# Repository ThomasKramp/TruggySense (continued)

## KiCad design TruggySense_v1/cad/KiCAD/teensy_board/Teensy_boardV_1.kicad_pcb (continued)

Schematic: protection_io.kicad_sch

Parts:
D18, D19, D34, D35, D36, D37, D38, D39: TVS_SMF3.3; SOD3718X108N
D40, D41, D42, D43, D44, D45, D46, D47: Zener_ZM4729A-GS18; D_MELF
F16, F17, F18, F19, F20, F21, F22, F23: SMD0805B010TF; Fuse_0805_2012Metric_Pad1.15x1.40mm_HandSolder

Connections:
/Encoder/Protection_IO/IN_1: D18.1 (K), F16.1; also elsewhere on the board
/Encoder/Protection_IO/IN_2: D19.1 (K), F17.1; also elsewhere on the board
/Encoder/Protection_IO/IN_3: D34.1 (K), F18.1; also elsewhere on the board
/Encoder/Protection_IO/IN_4: D35.1 (K), F19.1; also elsewhere on the board
/Encoder/Protection_IO/IN_5: D36.1 (K), F20.1; also elsewhere on the board
/Encoder/Protection_IO/IN_6: D37.1 (K), F21.1; also elsewhere on the board
/Encoder/Protection_IO/IN_7: D38.1 (K), F22.1; also elsewhere on the board
/Encoder/Protection_IO/IN_8: D39.1 (K), F23.1; also elsewhere on the board
/Encoder/Protection_IO/OUT_1: D40.1 (K), F16.2; also elsewhere on the board
/Encoder/Protection_IO/OUT_2: D41.1 (K), F17.2; also elsewhere on the board
/Encoder/Protection_IO/OUT_3: D42.1 (K), F18.2; also elsewhere on the board
/Encoder/Protection_IO/OUT_4: D43.1 (K), F19.2; also elsewhere on the board
/Encoder/Protection_IO/OUT_5: D44.1 (K), F20.2; also elsewhere on the board
/Encoder/Protection_IO/OUT_6: D45.1 (K), F21.2; also elsewhere on the board
/Encoder/Protection_IO/OUT_7: D46.1 (K), F22.2; also elsewhere on the board
/Encoder/Protection_IO/OUT_8: D47.1 (K), F23.2; also elsewhere on the board
GND: D18.2 (A), D19.2 (A), D34.2 (A), D35.2 (A), D36.2 (A), D37.2 (A), D38.2 (A), D39.2 (A), D40.2 (A), D41.2 (A), D42.2 (A), D43.2 (A), D44.2 (A), D45.2 (A), D46.2 (A), D47.2 (A); also elsewhere on the board

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
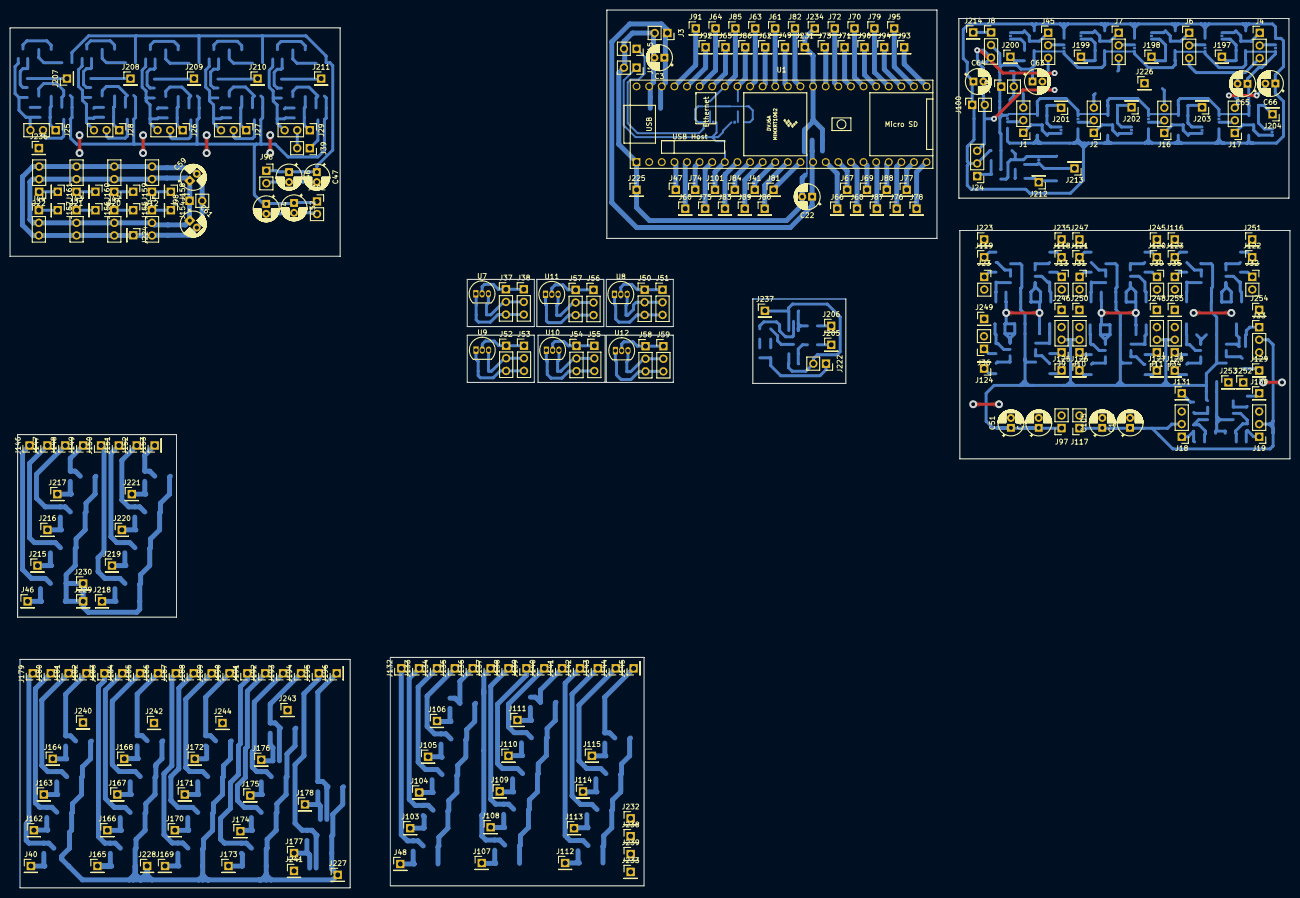
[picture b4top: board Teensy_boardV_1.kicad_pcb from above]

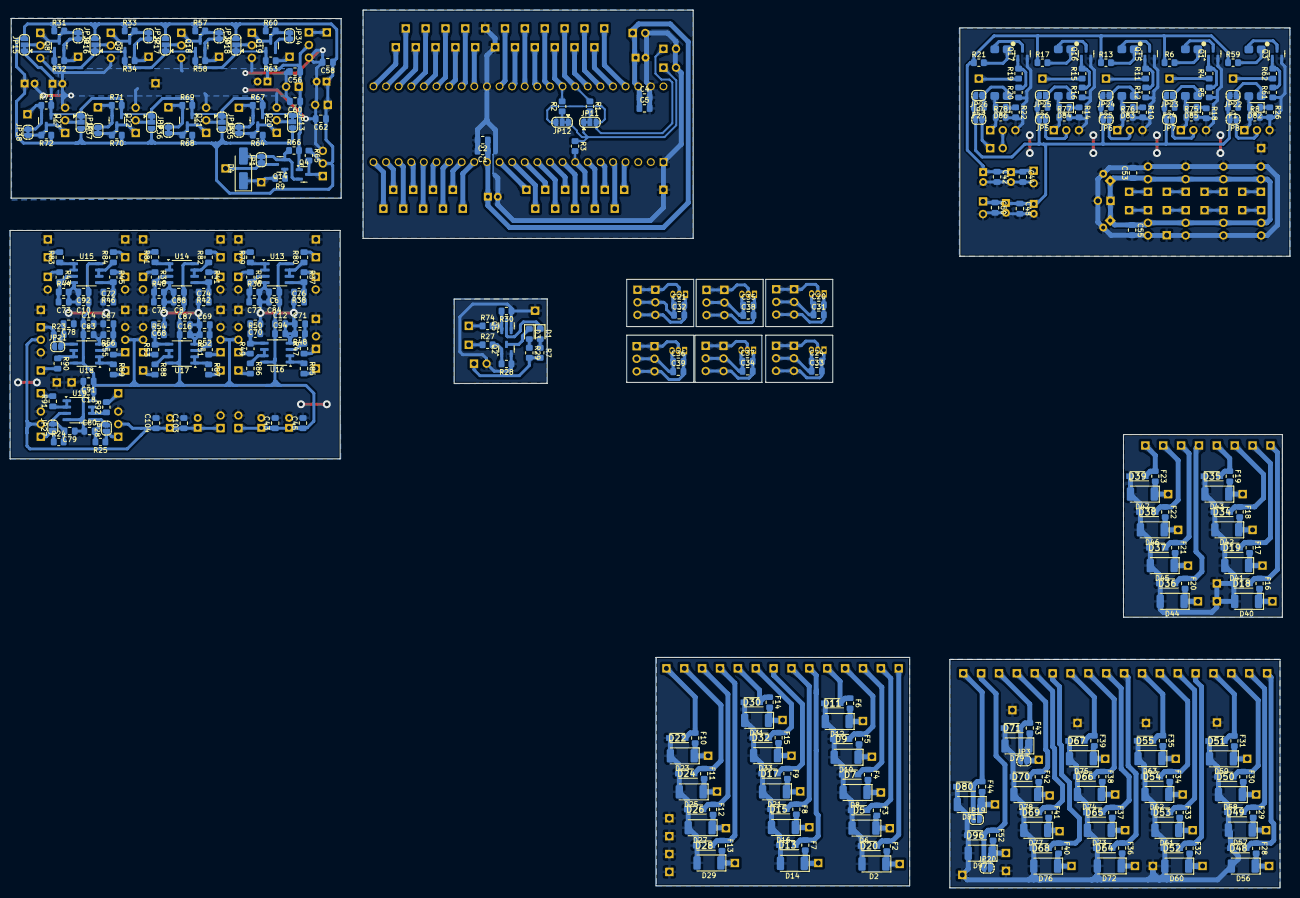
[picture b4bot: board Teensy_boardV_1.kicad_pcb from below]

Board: 2 copper layers, 257.8 x 176.8 mm, 625 parts (347 on the bottom side), 269 nets.

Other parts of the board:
C20, C21, C24, C34, C35, C36: 10µ; C_0805_2012Metric_Pad1.18x1.45mm_HandSolder
C31, C32, C33, C37, C38, C39: 10n; C_0805_2012Metric_Pad1.18x1.45mm_HandSolder
D48, D49, D50, D51, D52, D53, D54, D55, D64, D65, D66, D67, D68, D69, D70, D71, D80, D96: TVS_SMF3.3; SOD3718X108N
D56, D57, D58, D59, D60, D61, D62, D63, D72, D73, D74, D75, D76, D77, D78, D79, D81, D97: Zener_ZM4729A-GS18; D_MELF
F28, F29, F30, F31, F32, F33, F34, F35, F36, F37, F38, F39, F40, F41, F42, F43, F44, F52: SMD0805B010TF; Fuse_0805_2012Metric_Pad1.15x1.40mm_HandSolder
J37, J50, J52, J54, J56, J58: Temperature_module_in; PinHeader_1x03_P2.54mm_Vertical
J38, J51, J53, J55, J57, J59: Temperature_module_out; PinHeader_1x03_P2.54mm_Vertical
JP3, JP19, JP20: SolderJumper_2_Open; SolderJumper-2_P1.3mm_Open_RoundedPad1.0x1.5mm
U7, U8, U9, U10, U11, U12: DS18B20; TO-92_Inline

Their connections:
1_Wire_U: J37.1, J38.1, J50.1, J51.1, J52.1, J53.1, J54.1, J55.1, J56.1, J57.1, J58.1, J59.1, U7.2 (DQ), U8.2 (DQ), U9.2 (DQ), U10.2 (DQ), U11.2 (DQ), U12.2 (DQ); also elsewhere on the board
/Communication & pheripherals/Protection_IO1/IN_1: D48.1 (K), F28.1; also elsewhere on the board
/Communication & pheripherals/Protection_IO1/IN_2: D49.1 (K), F29.1; also elsewhere on the board
/Communication & pheripherals/Protection_IO1/IN_3: D50.1 (K), F30.1; also elsewhere on the board
/Communication & pheripherals/Protection_IO1/IN_4: D51.1 (K), F31.1; also elsewhere on the board
/Communication & pheripherals/Protection_IO1/IN_5: D52.1 (K), F32.1; also elsewhere on the board
/Communication & pheripherals/Protection_IO1/IN_6: D53.1 (K), F33.1; also elsewhere on the board
/Communication & pheripherals/Protection_IO1/IN_7: D54.1 (K), F34.1; also elsewhere on the board
/Communication & pheripherals/Protection_IO1/IN_8: D55.1 (K), F35.1; also elsewhere on the board
/Communication & pheripherals/Protection_IO1/IN_9: D64.1 (K), F36.1; also elsewhere on the board
/Communication & pheripherals/Protection_IO1/IN_10: D65.1 (K), F37.1; also elsewhere on the board
/Communication & pheripherals/Protection_IO1/IN_11: D66.1 (K), F38.1; also elsewhere on the board
/Communication & pheripherals/Protection_IO1/IN_12: D67.1 (K), F39.1; also elsewhere on the board
/Communication & pheripherals/Protection_IO1/IN_13: D68.1 (K), F40.1; also elsewhere on the board
/Communication & pheripherals/Protection_IO1/IN_14: D69.1 (K), F41.1; also elsewhere on the board
/Communication & pheripherals/Protection_IO1/IN_15: D70.1 (K), F42.1; also elsewhere on the board
/Communication & pheripherals/Protection_IO1/IN_16: D71.1 (K), F43.1, JP3.1 (A); also elsewhere on the board
/Communication & pheripherals/Protection_IO1/IN_17: D96.1 (K), F52.1, JP20.1 (A); also elsewhere on the board
/Communication & pheripherals/Protection_IO1/IN_18: D80.1 (K), F44.1, JP19.1 (A); also elsewhere on the board
/Communication & pheripherals/Protection_IO1/OUT_1: D56.1 (K), F28.2; also elsewhere on the board
/Communication & pheripherals/Protection_IO1/OUT_2: D57.1 (K), F29.2; also elsewhere on the board
/Communication & pheripherals/Protection_IO1/OUT_3: D58.1 (K), F30.2; also elsewhere on the board
/Communication & pheripherals/Protection_IO1/OUT_4: D59.1 (K), F31.2; also elsewhere on the board
/Communication & pheripherals/Protection_IO1/OUT_5: D60.1 (K), F32.2; also elsewhere on the board
/Communication & pheripherals/Protection_IO1/OUT_6: D61.1 (K), F33.2; also elsewhere on the board
/Communication & pheripherals/Protection_IO1/OUT_7: D62.1 (K), F34.2; also elsewhere on the board
/Communication & pheripherals/Protection_IO1/OUT_8: D63.1 (K), F35.2; also elsewhere on the board
/Communication & pheripherals/Protection_IO1/OUT_9: D72.1 (K), F36.2; also elsewhere on the board
/Communication & pheripherals/Protection_IO1/OUT_10: D73.1 (K), F37.2; also elsewhere on the board
/Communication & pheripherals/Protection_IO1/OUT_11: D74.1 (K), F38.2; also elsewhere on the board
/Communication & pheripherals/Protection_IO1/OUT_12: D75.1 (K), F39.2; also elsewhere on the board
/Communication & pheripherals/Protection_IO1/OUT_13: D76.1 (K), F40.2; also elsewhere on the board
/Communication & pheripherals/Protection_IO1/OUT_14: D77.1 (K), F41.2; also elsewhere on the board
/Communication & pheripherals/Protection_IO1/OUT_15: D78.1 (K), F42.2; also elsewhere on the board
/Communication & pheripherals/Protection_IO1/OUT_16: D79.1 (K), F43.2, JP3.2 (B); also elsewhere on the board
/Communication & pheripherals/Protection_IO1/OUT_17: D97.1 (K), F52.2, JP20.2 (B); also elsewhere on the board
/Communication & pheripherals/Protection_IO1/OUT_18: D81.1 (K), F44.2, JP19.2 (B); also elsewhere on the board
GND: C20.2, C21.2, C24.2, C31.2, C32.2, C33.2, C34.2, C35.2, C36.2, C37.2, C38.2, C39.2, D48.2 (A), D49.2 (A), D50.2 (A), D51.2 (A), D52.2 (A), D53.2 (A), D54.2 (A), D55.2 (A), D56.2 (A), D57.2 (A), D58.2 (A), D59.2 (A), D60.2 (A), D61.2 (A), D62.2 (A), D63.2 (A), D64.2 (A), D65.2 (A), D66.2 (A), D67.2 (A), D68.2 (A), D69.2 (A), D70.2 (A), D71.2 (A), D72.2 (A), D73.2 (A), D74.2 (A), D75.2 (A), D76.2 (A), D77.2 (A), D78.2 (A), D79.2 (A), D80.2 (A), D81.2 (A), D96.2 (A), D97.2 (A), J37.3, J38.3, J50.3, J51.3, J52.3, J53.3, J54.3, J55.3, J56.3, J57.3, J58.3, J59.3, U7.1 (GND), U8.1 (GND), U9.1 (GND), U10.1 (GND), U11.1 (GND), U12.1 (GND); also elsewhere on the board

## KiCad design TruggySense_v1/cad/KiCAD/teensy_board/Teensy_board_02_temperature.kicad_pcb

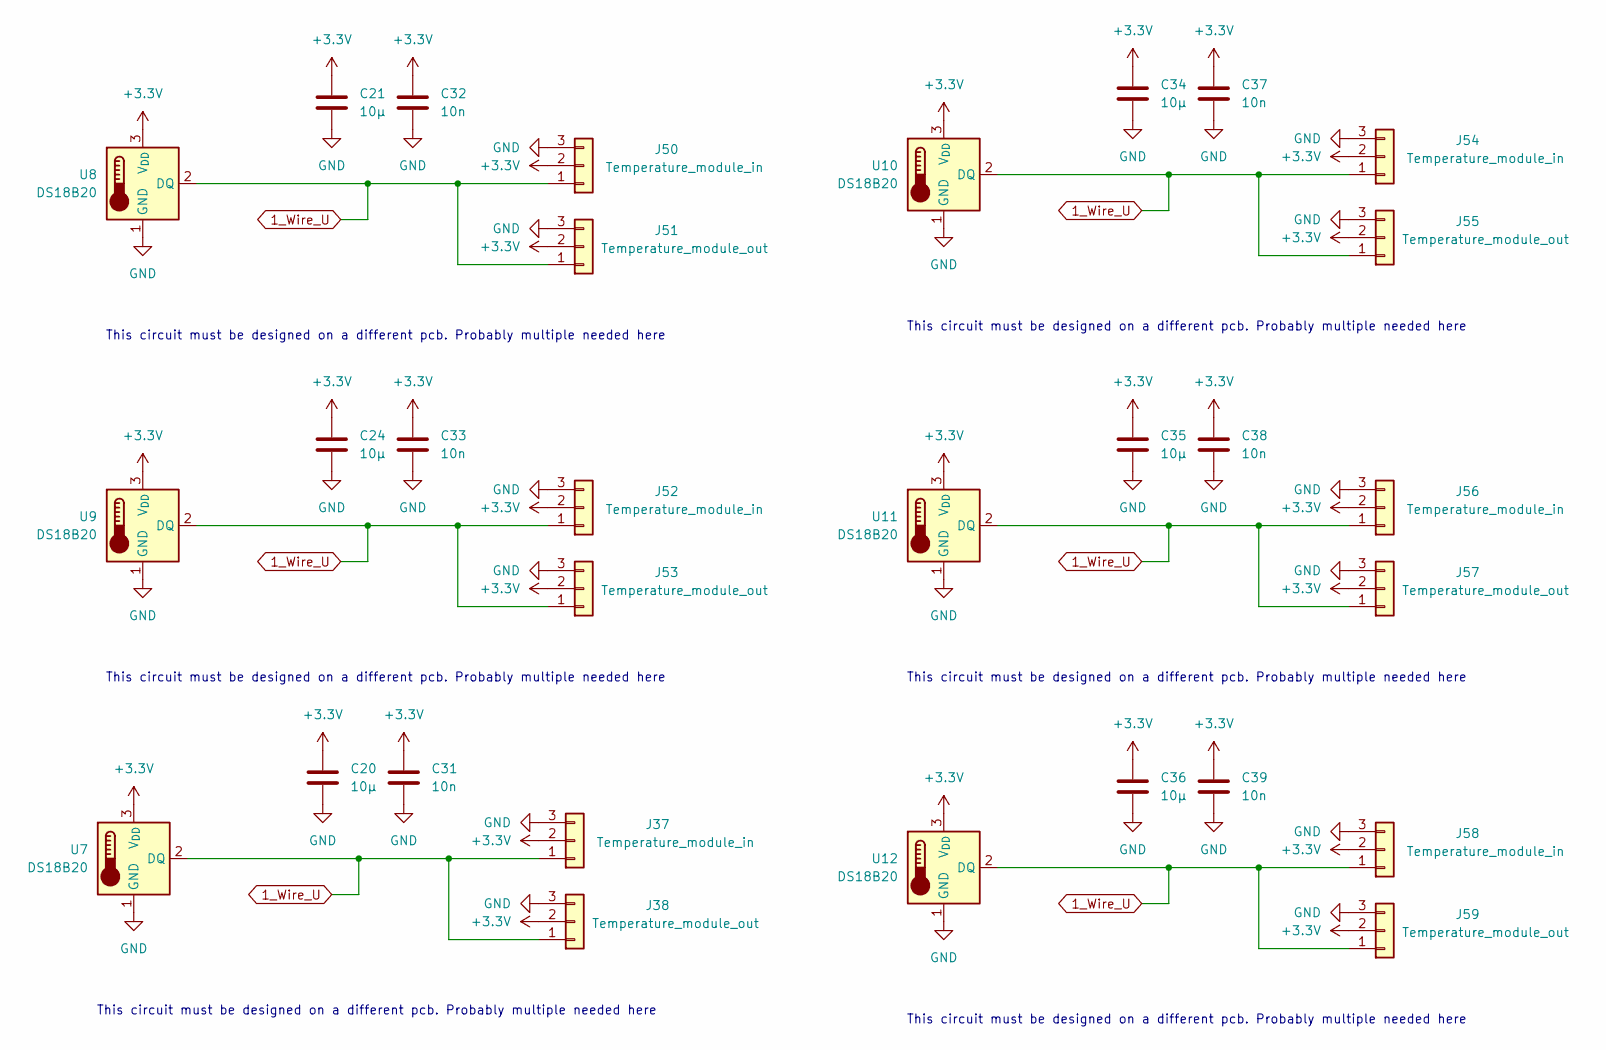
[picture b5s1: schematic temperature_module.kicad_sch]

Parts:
C20, C21, C24, C34, C35, C36: 10µ; C_0805_2012Metric_Pad1.18x1.45mm_HandSolder
C31, C32, C33, C37, C38, C39: 10n; C_0805_2012Metric_Pad1.18x1.45mm_HandSolder
J37, J50, J52, J54, J56, J58: Temperature_module_in; PinHeader_1x03_P2.54mm_Vertical
J38, J51, J53, J55, J57, J59: Temperature_module_out; PinHeader_1x03_P2.54mm_Vertical
U7, U8, U9, U10, U11, U12: DS18B20; TO-92_Inline

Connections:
1_Wire_U: J37.1, J38.1, J50.1, J51.1, J52.1, J53.1, J54.1, J55.1, J56.1, J57.1, J58.1, J59.1, U7.2 (DQ), U8.2 (DQ), U9.2 (DQ), U10.2 (DQ), U11.2 (DQ), U12.2 (DQ)
+3.3V: C20.1, C21.1, C24.1, C31.1, C32.1, C33.1, C34.1, C35.1, C36.1, C37.1, C38.1, C39.1, J37.2, J38.2, J50.2, J51.2, J52.2, J53.2, J54.2, J55.2, J56.2, J57.2, J58.2, J59.2, U7.3 (V_{DD}), U8.3 (V_{DD}), U9.3 (V_{DD}), U10.3 (V_{DD}), U11.3 (V_{DD}), U12.3 (V_{DD})
GND: C20.2, C21.2, C24.2, C31.2, C32.2, C33.2, C34.2, C35.2, C36.2, C37.2, C38.2, C39.2, J37.3, J38.3, J50.3, J51.3, J52.3, J53.3, J54.3, J55.3, J56.3, J57.3, J58.3, J59.3, U7.1 (GND), U8.1 (GND), U9.1 (GND), U10.1 (GND), U11.1 (GND), U12.1 (GND)

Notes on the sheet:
This circuit must be designed on a different pcb. Probably multiple needed here

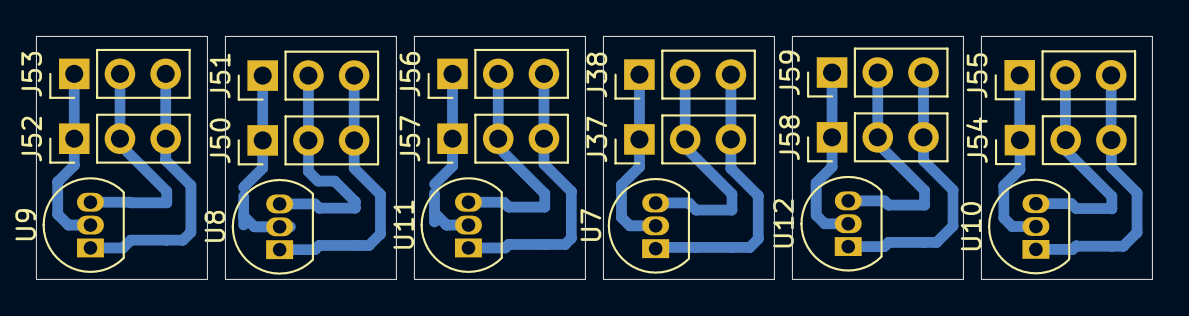
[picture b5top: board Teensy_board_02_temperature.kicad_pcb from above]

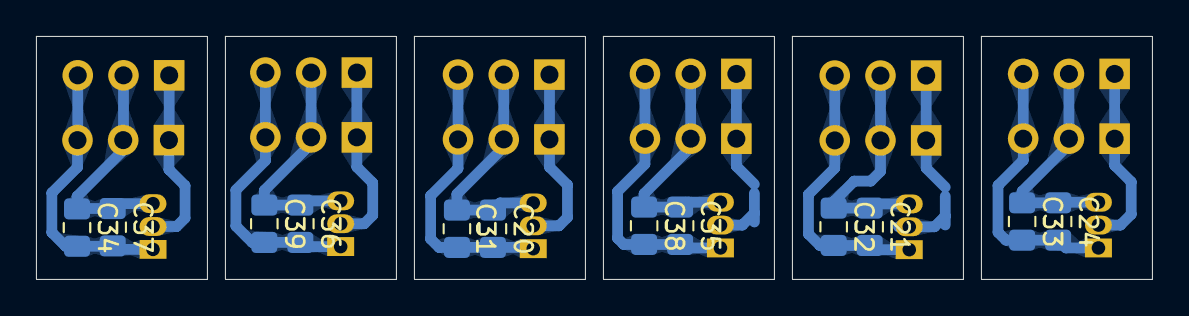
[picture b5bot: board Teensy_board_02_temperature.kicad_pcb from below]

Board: 2 copper layers, 62.0 x 13.5 mm, 30 parts (12 on the bottom side), 3 nets.
